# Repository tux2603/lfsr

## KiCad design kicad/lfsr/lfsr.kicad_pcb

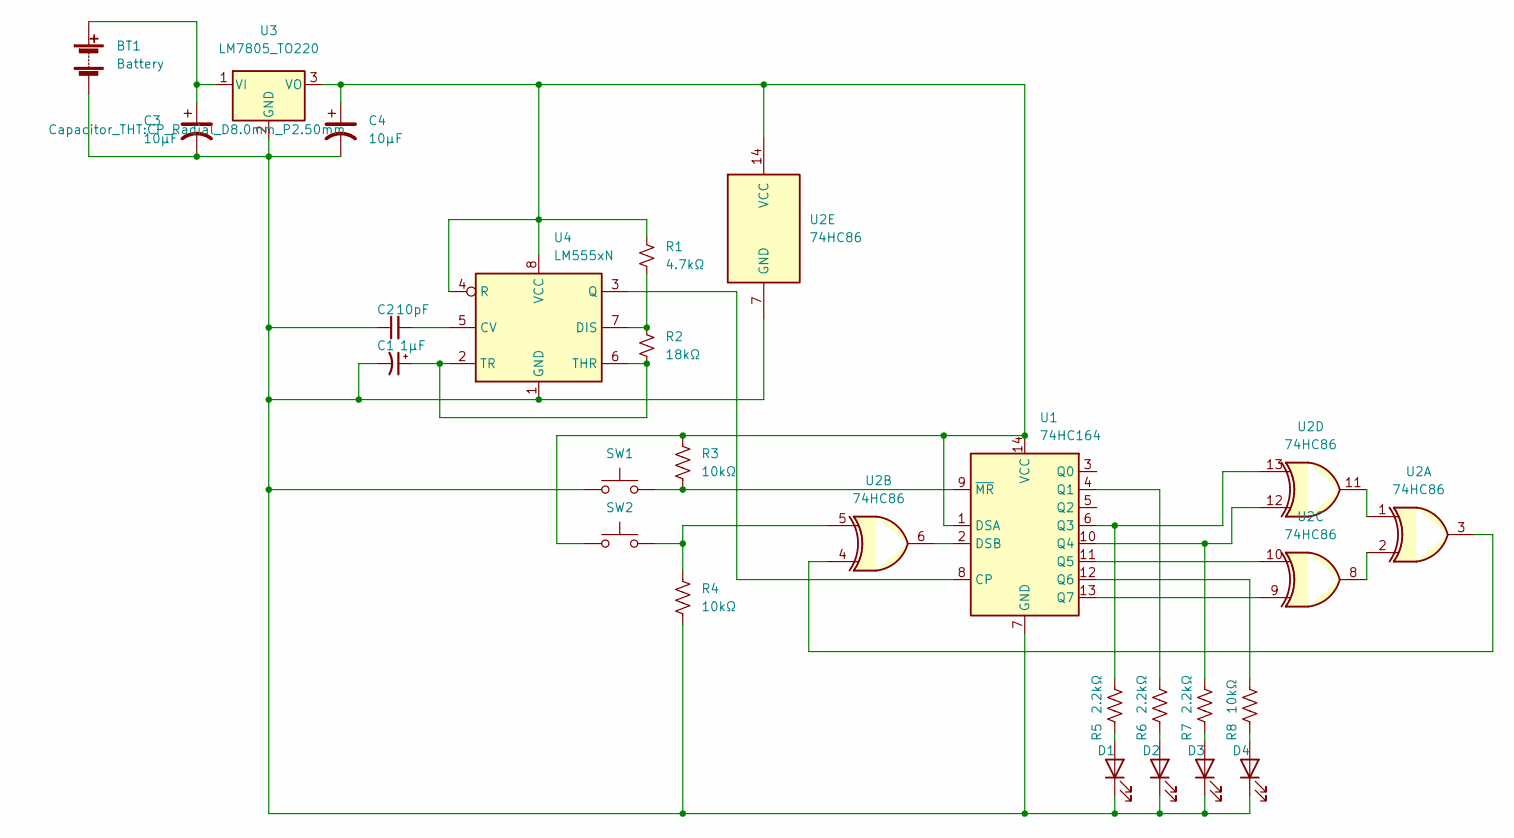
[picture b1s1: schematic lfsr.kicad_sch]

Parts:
BT1: Battery; SolderWire-0.1sqmm_1x02_P3.6mm_D0.4mm_OD1mm_Relief
C1: 1μF; CP_Radial_D5.0mm_P2.50mm
C2: 10pF; C_Disc_D4.3mm_W1.9mm_P5.00mm
C3, C4: 10μF; CP_Radial_D8.0mm_P2.50mm
D1, D2, D3, D4: LED; LED_D5.0mm
R1: 4.7kΩ; R_Axial_DIN0207_L6.3mm_D2.5mm_P2.54mm_Vertical
R2: 18kΩ; R_Axial_DIN0207_L6.3mm_D2.5mm_P2.54mm_Vertical
R3, R8: 10kΩ; R_Axial_DIN0207_L6.3mm_D2.5mm_P10.16mm_Horizontal
R4: 10kΩ; R_Axial_DIN0204_L3.6mm_D1.6mm_P7.62mm_Horizontal
R5, R6, R7: 2.2kΩ; R_Axial_DIN0207_L6.3mm_D2.5mm_P10.16mm_Horizontal
SW1, SW2: SW_Push; SW_Cherry_MX_1.00u_PCB
U1: 74HC164; DIP-14_W7.62mm_LongPads
U2: 74HC86; DIP-14_W7.62mm_LongPads
U3: LM7805_TO220; TO-220-3_Vertical
U4: LM555xN; DIP-8_W7.62mm

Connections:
unnamed: BT1.1 (+), C3.1, U3.1 (VI)
unnamed: BT1.2 (-), C1.2, C2.1, C3.2, C4.2, D1.1 (K), D2.1 (K), D3.1 (K), D4.1 (K), R4.2, SW1.1, U1.7 (GND), U2.7 (GND), U3.2 (GND), U4.1 (GND)
unnamed: C1.1, R2.2, U4.2 (TR), U4.6 (THR)
unnamed: C2.2, U4.5 (CV)
unnamed: D1.2 (A), R5.2
unnamed: D2.2 (A), R6.2
unnamed: D3.2 (A), R7.2
unnamed: D4.2 (A), R8.2
unnamed: R1.2, R2.1, U4.7 (DIS)
unnamed: C4.1, R1.1, R3.1, SW2.1, U1.1 (DSA), U1.14 (VCC), U2.14 (VCC), U3.3 (VO), U4.4 (R), U4.8 (VCC)
unnamed: R3.2, SW1.2, U1.9 (~MR)
unnamed: R4.1, SW2.2, U2.5
unnamed: R5.1, U1.6 (Q3), U2.13
unnamed: R6.1, U1.4 (Q1)
unnamed: R7.1, U1.10 (Q4), U2.12
unnamed: R8.1, U1.12 (Q6)
unnamed: U1.2 (DSB), U2.6
unnamed: U1.8 (CP), U4.3 (Q)
unnamed: U1.11 (Q5), U2.10
unnamed: U1.13 (Q7), U2.9
unnamed: U2.1, U2.11
unnamed: U2.3, U2.4
unnamed: U2.2, U2.8

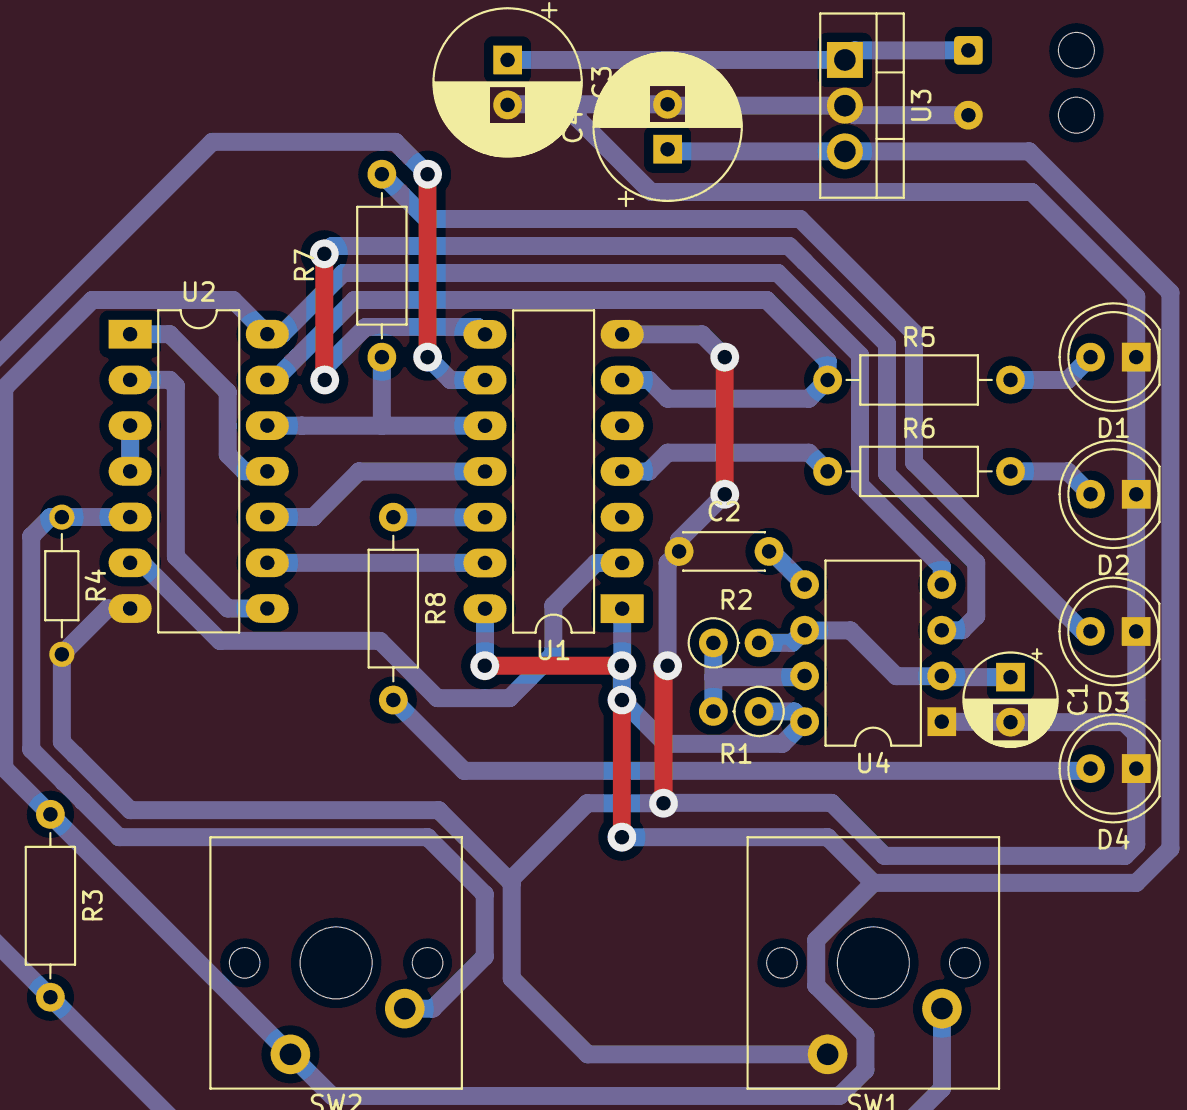
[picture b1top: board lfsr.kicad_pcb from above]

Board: 2 copper layers, 23 parts (1 on the bottom side), 23 nets.

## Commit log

2022-03-08 Initial design
2022-03-08 Ignore temp files and build logs
2022-03-08 Make things blink a bit faster
2022-03-08 74hc86 has an extra gate, so use it for the seed
    Not really necessary, but makes things more interesting.
    Also slow things back down just a little bit
2022-03-08 Change LED pins to make the traces easier to deal with
2022-03-08 Add kicad models
2022-03-11 Modify PCB design
    Swap things around so that traces are a minimum of 1mm wide instead of 0.1mm wide. 0.1mm traces didn't perform well on the router
